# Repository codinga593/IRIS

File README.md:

# IRIS
IRIS Is a high powered model rocket focused on a precise propulsive landing on a custom tower, similar to SpaceX's falcon 9. It will fly on a H45 motor to approximately 700m, guiding itself to a waypoint in the air using aerodynamic fin control. It will then begin a controlled descent where fins attempt to maintain x and y pos. A landing motor (F15) then ignites to kill velocity, as thrust vectoring helps guide it to the tower where it will be caught by two motorised arms.

This project, while ambitous will be split into serveral mid power and high power flights to test subsystems and more. At the heart of the rocket is the amethyst flight computer, along with two extra boards- a compute module 5 and a raspberry pi zero 2 w. The compute module five will run non linear model predicitive control, an insanely powerful control algorithm to determine required X and Y accels to reach the target given fin or tvc limits. The STM32 based flight computer then turns these accelerations into concrete actuator commands. AN ADDED layer of abstraction is present for the fins in the form of field oriented control, which maintains torque to prevent backdriving.

Pictured above: FULL CAD of IRIS with transparent airframe for visibility

Pictured above: AMETHYST rocket flight computer. Note: Silkscreen colour is subject to change.

Pictured Above: Final Avionics Bay design on IRIS

# Bill of Materials (BOM)

| Designator | Part Name | Qty | Value / Part Number | Link |
|---|---:|---:|---|---|
| C66,C95,C26,C49,C28,C67,C55,C29,C33,C22,C48,C54,C19,C34,C30,C58,C41,C42,C20,C45,C46,C39,C18,C93,C47,C32,C21,C25,C27,C88,C35 | Ceramic Capacitor | 31 | 100nF, 0402, Samsung CL05B104KO5NNNC (JLC C1525) | [Link](https://jlcpcb.com/partdetail/1877-CL05B104KO5NNNC/C1525) |
| C23,C24,C61,C60 | Ceramic Capacitor | 4 | 24pF, 0402, C0G/NP0, FH 0402CG240J500NT (LCSC C1553) | [Link](https://www.lcsc.com/product-detail/C1553.html) |
| U3 | IMU | 1 | BNO085 (JLC C5189642) | [Link](https://jlcpcb.com/partdetail/CEVA-BNO085/C5189642) |
| J9,J1,J10,J11 | Socket Header | 4 | 1x03, 2.54mm, vertical, Amphenol SIP050-1X03-157BLF | [Link](https://www.digikey.com/en/products/detail/amphenol-cs-fci/SIP050-1X03-157BLF/1541044) |
| R45,R48,R46,R47,R49,R44 | Resistor | 6 | TBD - source BOM only says 'R' (exact value not specified) |  |
| R21,R14,R22,R17 | Resistor | 4 | 4.7kΩ, 0603, UNI-ROYAL 0603WAF4701T5E (LCSC C23162) | [Link](https://www.lcsc.com/product-detail/C23162.html) |
| TP13,TP9,TP14,TP6,TP11,TP10,TP16,TP15,TP5,TP8,TP7 | Test Point | 11 | PCB test pad 1.0x1.0mm - no discrete purchasable part specified |  |
| URpiZero1,UCM4 | Socket Header | 2 | 2x20 Raspberry Pi socket/riser header, Adafruit 4079 | [Link](https://www.digikey.com.au/en/products/detail/adafruit-industries-llc/4079/9858462) |
| R10,R18,R28 | Resistor | 3 | 100kΩ, 0402, UNI-ROYAL 0402WGF1003TCE (JLC/LCSC C25741) | [Link](https://www.lcsc.com/product-detail/C25741.html) |
| Q2,Q4,Q3 | MOSFET | 3 | BSZ100N06LS3 G, Infineon | [Link](https://www.digikey.com/en/products/detail/infineon-technologies/BSZ100N06LS3GATMA1/1936392) |
| C53,C92,C90,C94 | Ceramic Capacitor | 4 | 10uF, 0402, Samsung CL05A106MQ5NUNC (JLC C15525) | [Link](https://jlcpcb.com/partdetail/16204-CL05A106MQ5NUNC/C15525) |
| R6,R32,R8,R1 | Resistor | 4 | 100Ω, 0402, Ever Ohms CR0402F100RQ10 (JLC C429511) | [Link](https://jlcpcb.com/partdetail/Ever_OhmsTech-CR0402F100RQ10/C429511) |
| J14 | Pin Header | 1 | 1x04, 2.54mm, vertical, generic 4-pin header | [Link](https://newhavendisplay.com/1x4-single-row-pin-header-connector/) |
| J17 | RF Connector | 1 | Hirose U.FL-R-SMT(01) | [Link](https://www.digikey.com.au/en/products/detail/hirose-electric-co-ltd/U-FL-R-SMT-01/513010) |
| U5 | Barometer | 1 | MS5611-01BA03 / MS561101BA03-50 (JLC C15639) | [Link](https://jlcpcb.com/partdetail/TEConnectivity-MS561101BA0350/C15639) |
| C37 | Ceramic Capacitor | 1 | 10uF, 0603, Samsung CL10A106MA8NRNC (LCSC C96446) | [Link](https://www.lcsc.com/product-detail/C96446.html) |
| C91,C86,C89 | Ceramic Capacitor | 3 | 22uF, 0402, JLCPCB Assembly 22uF/16V (JLC C9900105298) | [Link](https://jlcpcb.com/partdetail/JLCPCBAssembly-22uF16V/C9900105298) |
| C84,C85 | Ceramic Capacitor | 2 | 10pF, 0402, FH 0402CG100J500NT (JLC C1545) | [Link](https://jlcpcb.com/partdetail/1897-0402CG100J500NT/C1545) |
| L11,L10,L9 | Inductor | 3 | 6.8uH, Würth WE-XHMA 6060 | [Link](https://www.mouser.com/ProductDetail/Wurth-Elektronik/74437368068) |
| R34,R33 | Resistor | 2 | 22Ω, 0402, YAGEO RC0402FR-0722RL (LCSC C114765) | [Link](https://www.lcsc.com/product-detail/C114765.html) |
| J5,J3,J4 | Terminal Block | 3 | Same Sky / CUI TB002-500-02BE | [Link](https://www.digikey.com.au/en/products/detail/same-sky-formerly-cui-devices/TB002-500-02BE/10064069) |
| Y1,Y3 | Crystal | 2 | 24MHz, 3225, Suzhou Liming 3225-24.00-20-10-10/A (JLC C518165) | [Link](https://jlcpcb.com/partdetail/534702-3225_24_00_20_10_10A/C518165) |
| C31 | Ceramic Capacitor | 1 | 10uF, 0402, Samsung CL05A106MQ5NUNC (JLC C15525) | [Link](https://jlcpcb.com/partdetail/16204-CL05A106MQ5NUNC/C15525) |
| J6 | JST Header | 1 | JST B5B-XH-A, 5-pin, 2.50mm, vertical | [Link](https://www.digikey.com/en/products/detail/jst-sales-america-inc/B5B-XH-A/1530483) |
| IC2 | LoRa Module | 1 | Seeed 114993390 / Wio-SX1262 | [Link](https://www.digikey.com/en/products/detail/seeed-technology-co-ltd/114993390/25835823) |
| U2 | LDO Regulator | 1 | AMS1117-3.3, SOT-223 (JLC C6186) | [Link](https://jlcpcb.com/partdetail/Advanced_MonolithicSystems-AMS1117_33/C6186) |
| U4 | IMU | 1 | ICM-42688-P (JLC C1850418) | [Link](https://jlcpcb.com/partdetail/TDKInvenSense-ICM_42688P/C1850418) |
| U11,U12,U13 | Buck Converter | 3 | TPS54525PWPR (JLC C140350) | [Link](https://jlcpcb.com/partdetail/TexasInstruments-TPS54525PWPR/C140350) |
| C36,C38,C56 | Ceramic Capacitor | 3 | 100nF, 0603, YAGEO CC0603KRX7R9BB104 (LCSC C14663) | [Link](https://www.lcsc.com/product-detail/C14663.html) |
| IC1 | NOR Flash | 1 | W25Q128JVFIQ (JLC C111478) | [Link](https://jlcpcb.com/partdetail/WinbondElec-W25Q128JVFIQ/C111478) |
| R15,R2,R7,R9,R11,R5,R29,R12,R27 | Resistor | 9 | 10kΩ, 0402, UNI-ROYAL 0402WGF1002TCE (JLC C25744) | [Link](https://jlcpcb.com/partdetail/26487-0402WGF1002TCE/C25744) |
| R3,R4 | Resistor | 2 | 1.5kΩ, 0402, UNI-ROYAL 0402WGF1501TCE (LCSC C25867) | [Link](https://www.lcsc.com/product-detail/C25867.html) |
| U1 | MCU | 1 | STM32H753ZIT6 (JLC C730207) | [Link](https://jlcpcb.com/partdetail/STMicroelectronics-STM32H753ZIT6/C730207) |
| C3,C2 | Ceramic Capacitor | 2 | 22uF, 0805, Samsung CL21A226MAYNNNE (LCSC C45783) | [Link](https://www.lcsc.com/product-detail/C45783.html) |
| C59 | Ceramic Capacitor | 1 | 10nF, 0402, Kyocera AVX 0402YC103K4T2A (JLC C2172121) | [Link](https://jlcpcb.com/partdetail/KyoceraAVX-0402YC103K4T2A/C2172121) |
| Y4 | Crystal | 1 | TBD - source BOM says only 'Crystal' in 2012 package |  |
| IC7 | Radar Sensor | 1 | Acconeer A121-001-T&R / A121 | [Link](https://www.mouser.com/ProductDetail/Acconeer/A121-001-TR) |
| D2 | LED | 1 | TBD - source BOM says only 'LED' in 0402 package |  |
| C1 | Ceramic Capacitor | 1 | 10uF, 0402, Samsung CL05A106MQ5NUNC (JLC C15525) | [Link](https://jlcpcb.com/partdetail/16204-CL05A106MQ5NUNC/C15525) |
| J7 | Molex PicoBlade Header | 1 | Molex 53261-0471 | [Link](https://www.digikey.com/en/products/detail/molex/0532610471/699096) |
| C40,C17 | Ceramic Capacitor | 2 | 2.2uF, 0402, Samsung CL05A225MQ5NSNC (JLC C12530) | [Link](https://jlcpcb.com/partdetail/13164-CL05A225MQ5NSNC/C12530) |
| J18 | USB Connector | 1 | Würth 629105150521, Micro USB B | [Link](https://www.digikey.com.au/en/products/detail/w%C3%BCrth-elektronik/629105150521/5047751) |
| U7 | Level Shifter | 1 | TXS0108EPWR (JLC C17206) | [Link](https://jlcpcb.com/partdetail/TexasInstruments-TXS0108EPWR/C17206) |
| FB1 | Ferrite Bead | 1 | Sunlord GZ1608D601TF (JLC C1002) | [Link](https://jlcpcb.com/partdetail/Sunlord-GZ1608D601TF/C1002) |
| D3 | Schottky Diode | 1 | BAT54A, SOT-23 (JLC C397609) | [Link](https://jlcpcb.com/partdetail/AnBon-BAT54A/C397609) |
| J12 | JST Header | 1 | JST S2B-XH-A, 2-pin, 2.50mm, right-angle | [Link](https://www.digikey.com/en/products/detail/jst-sales-america-inc/S2B-XH-A/1651055) |
| U10 | GNSS Module | 1 | u-blox MAX-M10S-00B (JLC C4153167) | [Link](https://jlcpcb.com/partdetail/UBLOX-MAX_M10S00B/C4153167) |
| J8 | XT30 Connector | 1 | AMASS XT30U-M (JLC C99101) | [Link](https://jlcpcb.com/partdetail/Changzhou_AmassElec-XT30UM/C99101) |
| R20,R19 | Resistor | 2 | 10kΩ, 0603, YAGEO RC0603FR-0710KL (LCSC C98220) | [Link](https://www.lcsc.com/product-detail/C98220.html) |
| J2 | JST Header | 1 | JST B2B-XH-A, 2-pin, 2.50mm, vertical | [Link](https://www.digikey.com/en/products/detail/jst-sales-america-inc/B2B-XH-A/1651045) |

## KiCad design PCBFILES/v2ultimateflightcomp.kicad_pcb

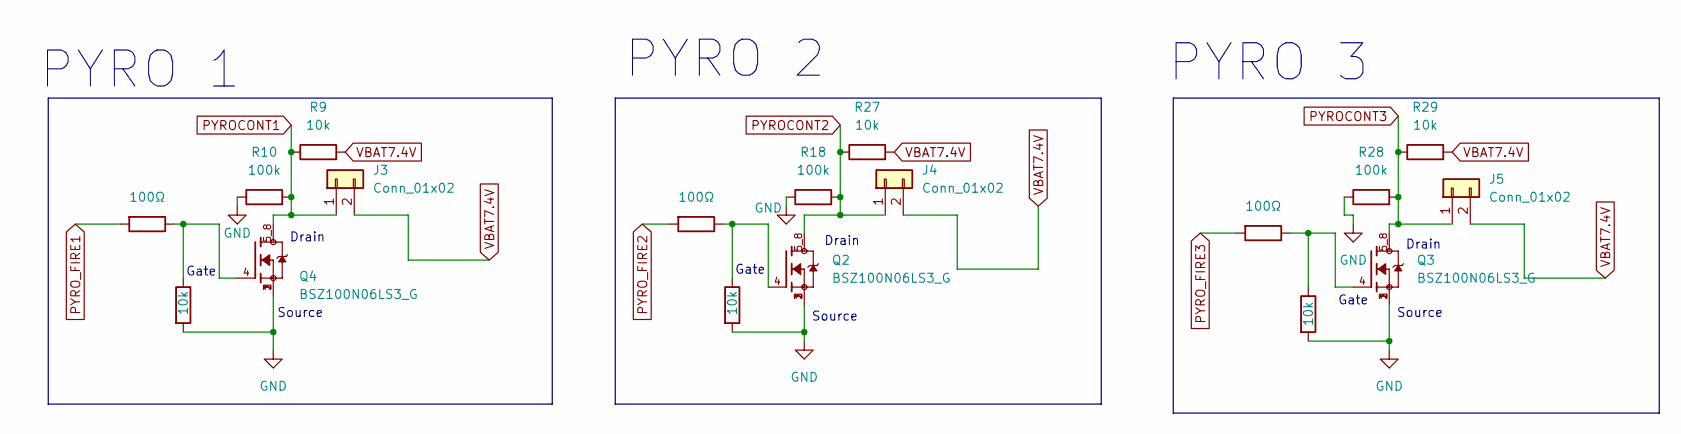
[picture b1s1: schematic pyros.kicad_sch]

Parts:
J3, J4, J5: Conn_01x02; CUI_TB002-500-02BE
Q2, Q3, Q4: BSZ100N06LS3_G; TRANS_BSZ100N06LS3_G; PARTREV 2.4
R1, R6, R8: 100Ω; R_0402_1005Metric
R2, R5, R7, R9, R27, R29: 10k; R_0402_1005Metric
R10, R18, R28: 100k; R_0402_1005Metric

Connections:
GND: Q2.1, Q2.2, Q2.3, Q3.1, Q3.2, Q3.3, Q4.1, Q4.2, Q4.3, R2.2, R5.2, R7.2, R10.1, R18.1, R28.1; also elsewhere on the board
unnamed: Q2.4, R5.1, R6.1
unnamed: Q3.4, R7.1, R8.1
unnamed: Q4.4, R1.1, R2.1
PYROCONT1: J3.1, Q4.5_8, R9.1, R10.2; also elsewhere on the board
PYROCONT2: J4.1, Q2.5_8, R18.2, R27.1; also elsewhere on the board
PYROCONT3: J5.1, Q3.5_8, R28.2, R29.1; also elsewhere on the board
PYRO_FIRE1: R1.2; also elsewhere on the board
PYRO_FIRE2: R6.2; also elsewhere on the board
PYRO_FIRE3: R8.2; also elsewhere on the board
VBAT7.4V: J3.2, J4.2, J5.2, R9.2, R27.2, R29.2; also elsewhere on the board

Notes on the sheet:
PYRO 3
Gate
PYRO 2
Source
Drain
PYRO 1

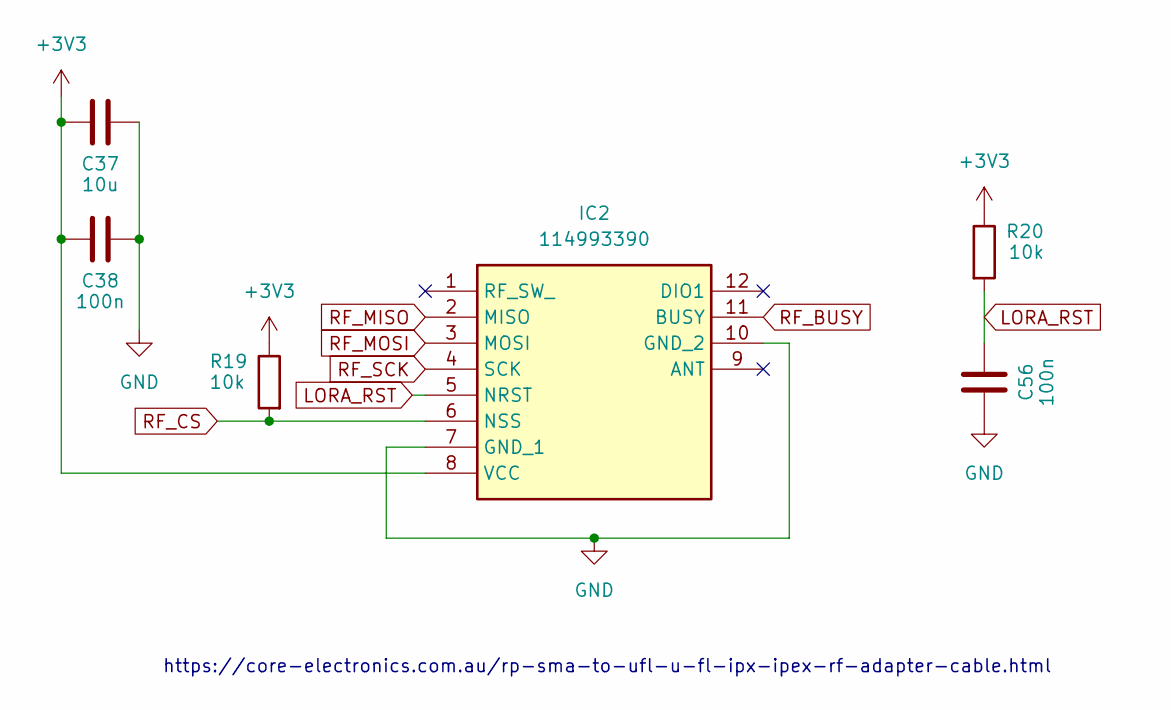
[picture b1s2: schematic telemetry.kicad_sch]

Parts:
C37: 10u; C_0603_1608Metric
C38, C56: 100n; C_0603_1608Metric
IC2: 114993390; Mouser Part Number 713-114993390
R19, R20: 10k; R_0603_1608Metric

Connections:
+3V3: C37.1, C38.1, IC2.8 (VCC), R19.1, R20.1; also elsewhere on the board
GND: C37.2, C38.2, C56.1, IC2.7 (GND_1), IC2.10 (GND_2); also elsewhere on the board
LORA_RST: C56.2, IC2.5 (NRST), R20.2; also elsewhere on the board
RF_BUSY: IC2.11 (BUSY); also elsewhere on the board
RF_CS: IC2.6 (NSS), R19.2; also elsewhere on the board
RF_MISO: IC2.2 (MISO); also elsewhere on the board
RF_MOSI: IC2.3 (MOSI); also elsewhere on the board
RF_SCK: IC2.4 (SCK); also elsewhere on the board

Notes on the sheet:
https://core-electronics.com.au/rp-sma-to-ufl-u-fl-ipx-ipex-rf-adapter-cable.html

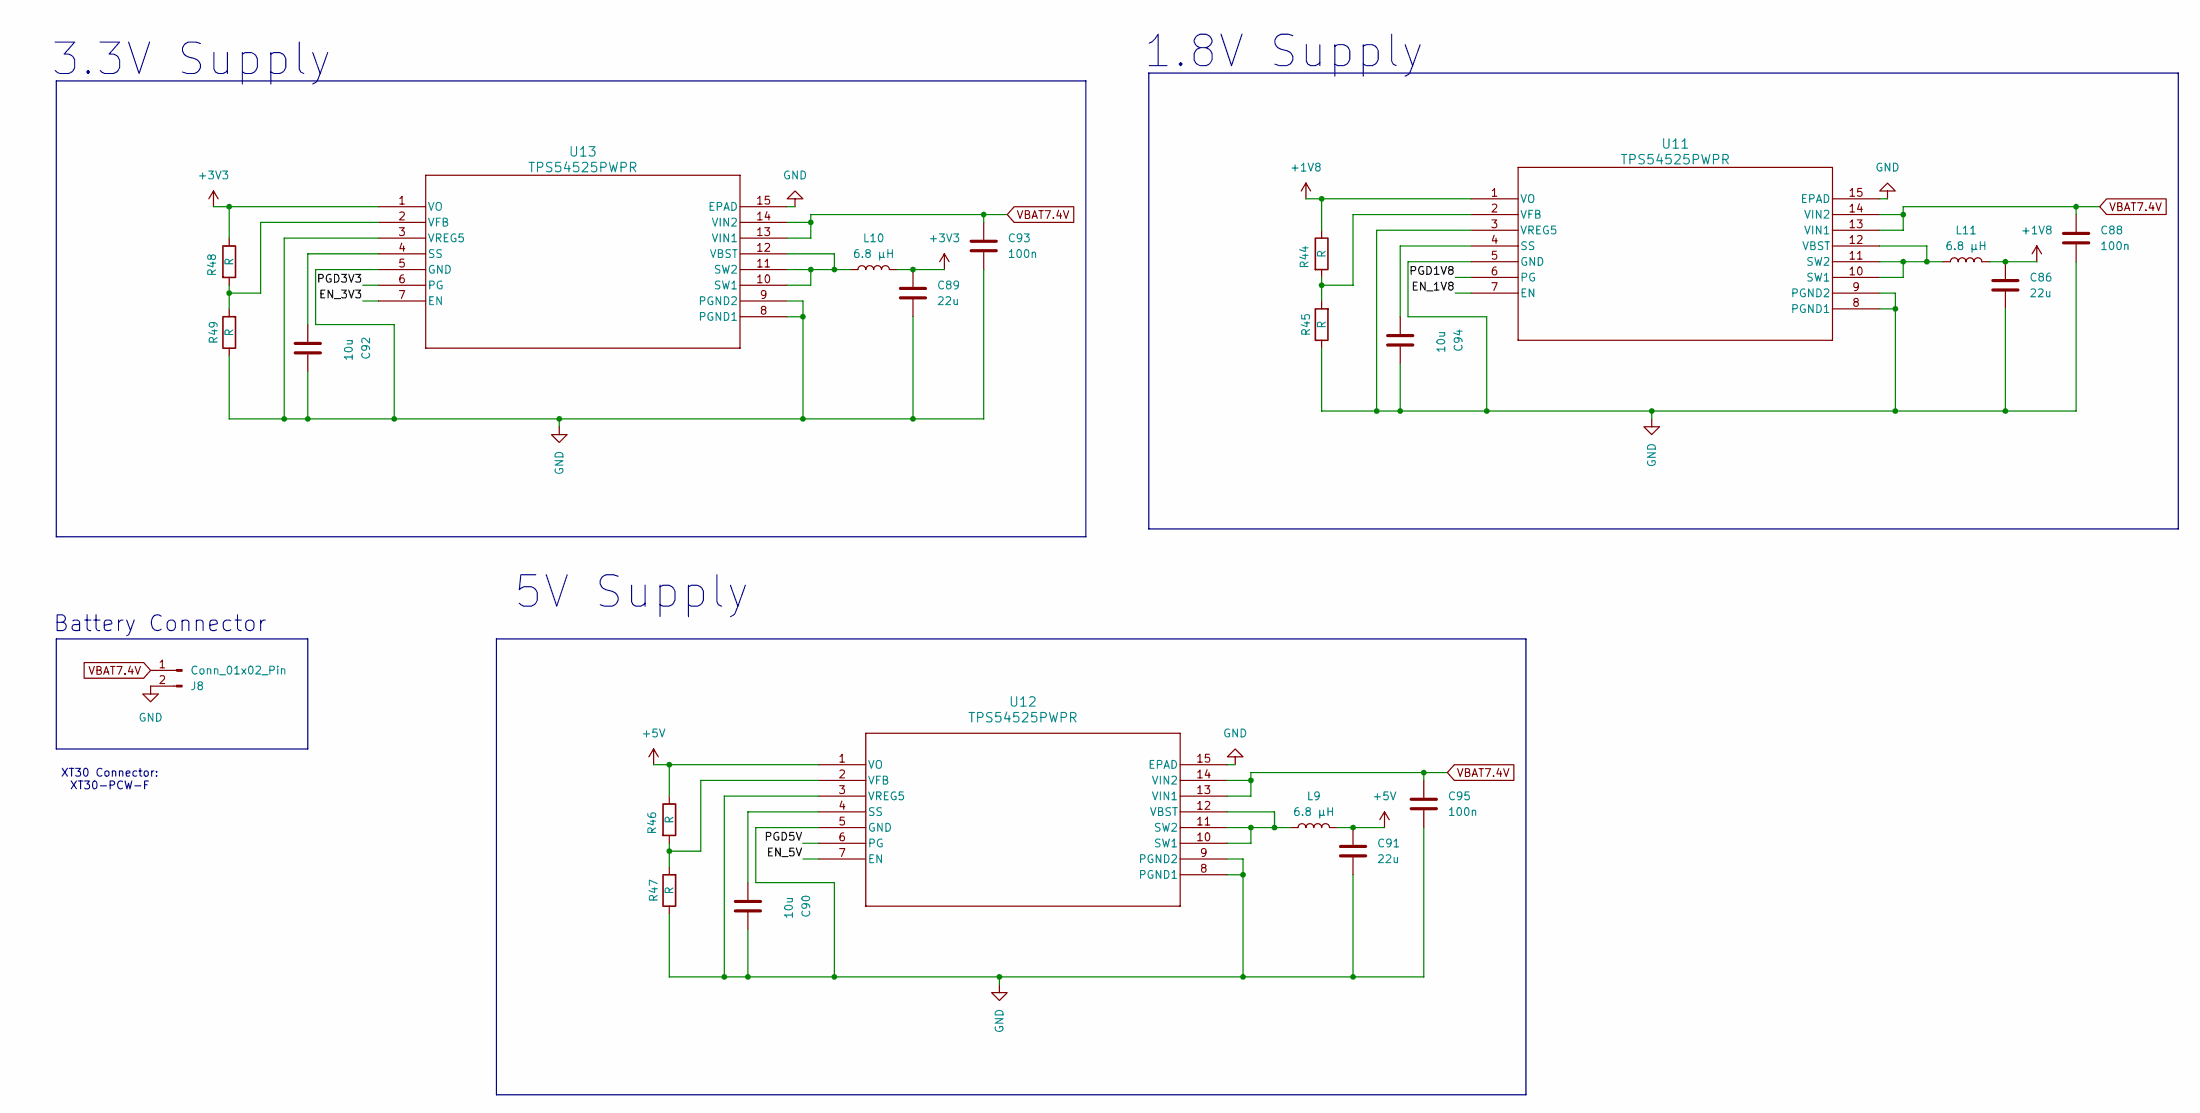
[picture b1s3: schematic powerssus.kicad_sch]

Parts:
C86, C89, C91: 22u; C_0402_1005Metric
C88, C93, C95: 100n; C_0402_1005Metric
C90, C92, C94: 10u; C_0402_1005Metric
J8: Conn_01x02_Pin; AMASS_XT30U-M_1x02_P5.0mm_Vertical
L9, L10, L11: 6.8 µH; WE-XHMA_6060
R44, R45, R46, R47, R48, R49: R; R_0402_1005Metric
U11, U12, U13: TPS54525PWPR; PWP14_2P31X2P46_TEX

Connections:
+1V8: C86.1, L11.2, R44.1, U11.1 (VO); also elsewhere on the board
+3V3: C89.1, L10.2, R48.1, U13.1 (VO); also elsewhere on the board
+5V: C91.1, L9.2, R46.1, U12.1 (VO); also elsewhere on the board
/Power/EN_1V8: U11.7 (EN)
/Power/EN_3V3: U13.7 (EN)
/Power/EN_5V: U12.7 (EN)
/Power/PGD1V8: U11.6 (PG)
/Power/PGD3V3: U13.6 (PG)
/Power/PGD5V: U12.6 (PG)
GND: C86.2, C88.2, C89.2, C90.1, C91.2, C92.1, C93.2, C94.1, C95.2, J8.2, R45.1, R47.1, R49.1, U11.3 (VREG5), U11.5 (GND), U11.8 (PGND1), U11.9 (PGND2), U11.15 (EPAD), U12.3 (VREG5), U12.5 (GND), U12.8 (PGND1), U12.9 (PGND2), U12.15 (EPAD), U13.3 (VREG5), U13.5 (GND), U13.8 (PGND1), U13.9 (PGND2), U13.15 (EPAD); also elsewhere on the board
unnamed: C94.2, U11.4 (SS)
unnamed: L11.1, U11.10 (SW1), U11.11 (SW2), U11.12 (VBST)
unnamed: R44.2, R45.2, U11.2 (VFB)
unnamed: C90.2, U12.4 (SS)
unnamed: L9.1, U12.10 (SW1), U12.11 (SW2), U12.12 (VBST)
unnamed: R46.2, R47.2, U12.2 (VFB)
unnamed: C92.2, U13.4 (SS)
unnamed: L10.1, U13.10 (SW1), U13.11 (SW2), U13.12 (VBST)
unnamed: R48.2, R49.2, U13.2 (VFB)
VBAT7.4V: C88.1, C93.1, C95.1, J8.1, U11.13 (VIN1), U11.14 (VIN2), U12.13 (VIN1), U12.14 (VIN2), U13.13 (VIN1), U13.14 (VIN2); also elsewhere on the board

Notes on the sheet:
5V Supply
1.8V Supply
XT30 Connector: XT30-PCW-F
3.3V Supply
Battery Connector

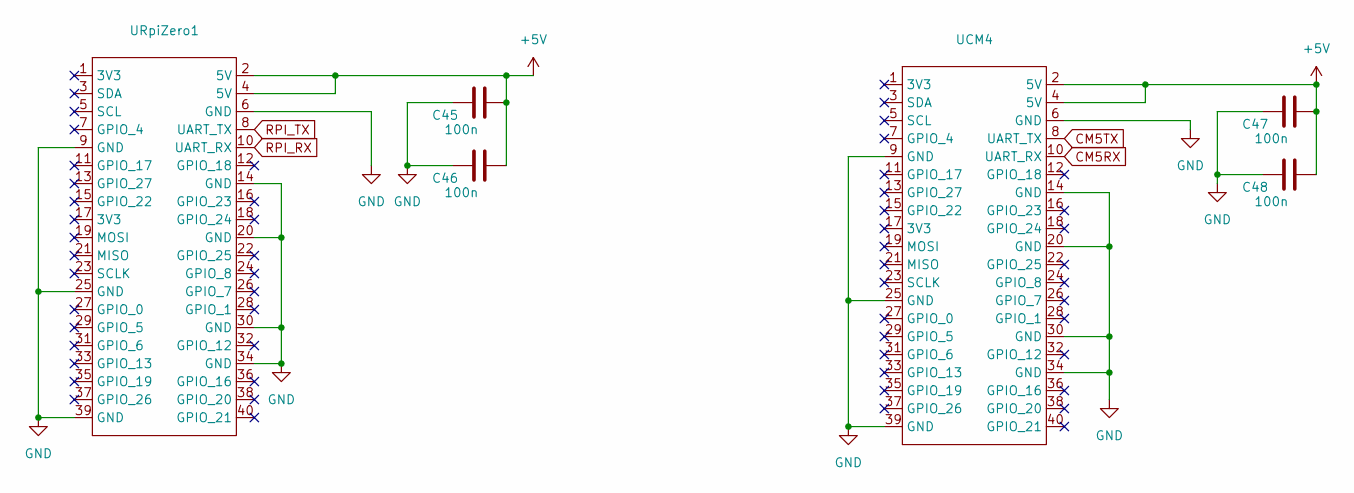
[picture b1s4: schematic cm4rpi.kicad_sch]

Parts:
C45, C46, C47, C48: 100n; C_0402_1005Metric
UCM4: PinSocket_2x20_P2.54mm_Vertical_SMD
URpiZero1: PinSocket_2x20_P2.54mm_Vertical_SMD

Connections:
+5V: C45.2, C46.2, C47.2, C48.2, UCM4.2 (5V), UCM4.4 (5V), URpiZero1.2 (5V), URpiZero1.4 (5V); also elsewhere on the board
CM5RX: UCM4.10 (UART_RX); also elsewhere on the board
CM5TX: UCM4.8 (UART_TX); also elsewhere on the board
GND: C45.1, C46.1, C47.1, C48.1, UCM4.6 (GND), UCM4.9 (GND), UCM4.14 (GND), UCM4.20 (GND), UCM4.25 (GND), UCM4.30 (GND), UCM4.34 (GND), UCM4.39 (GND), URpiZero1.6 (GND), URpiZero1.9 (GND), URpiZero1.14 (GND), URpiZero1.20 (GND), URpiZero1.25 (GND), URpiZero1.30 (GND), URpiZero1.34 (GND), URpiZero1.39 (GND); also elsewhere on the board
RPI_RX: URpiZero1.10 (UART_RX); also elsewhere on the board
RPI_TX: URpiZero1.8 (UART_TX); also elsewhere on the board

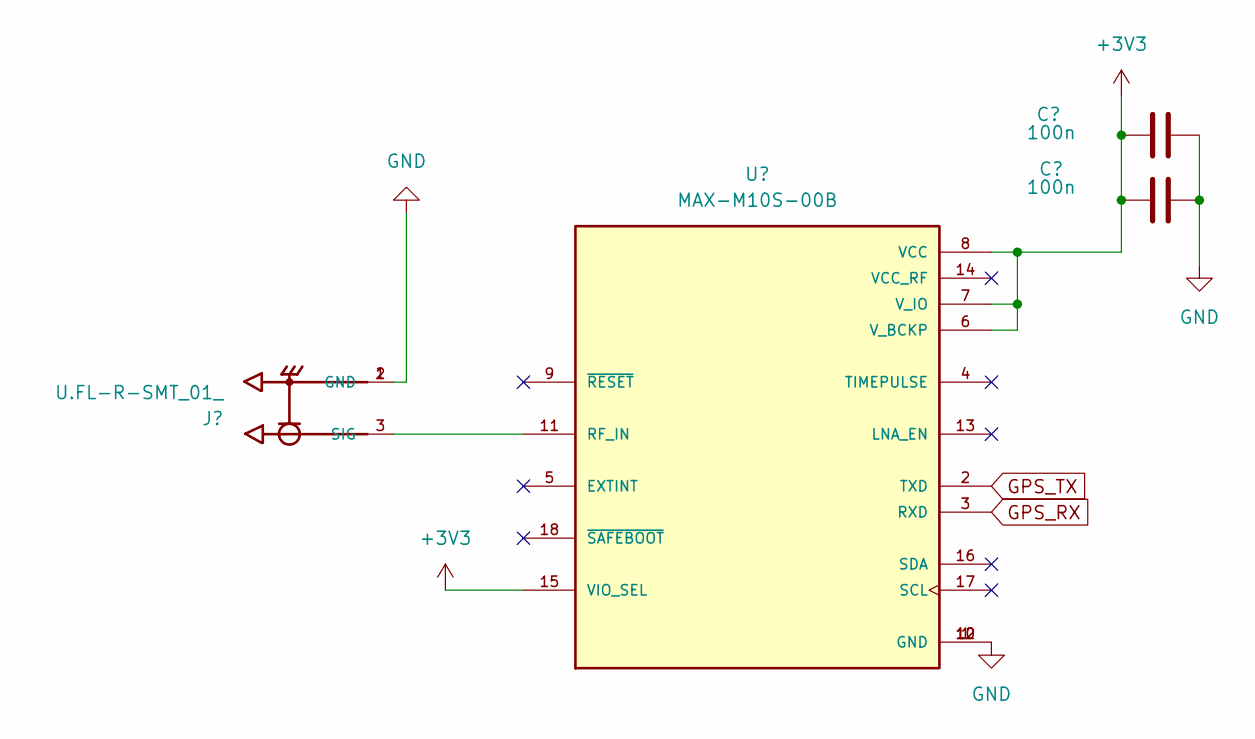
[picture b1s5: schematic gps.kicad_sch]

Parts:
C54, C55: 100n; C_0402_1005Metric
J17: U.FL-R-SMT_01_; HRS_U.FL-R-SMT_01_
U10: MAX-M10S-00B; XCVR_MAX-M10S-00B; PARTREV C1

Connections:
+3V3: C54.1, C55.1, U10.6 (V_BCKP), U10.7 (V_IO), U10.8 (VCC), U10.15 (VIO_SEL); also elsewhere on the board
GND: C54.2, C55.2, J17.1 (GND), J17.2 (GND), U10.1 (GND), U10.10 (GND), U10.12 (GND); also elsewhere on the board
GPS_RX: U10.3 (RXD); also elsewhere on the board
GPS_TX: U10.2 (TXD); also elsewhere on the board
unnamed: J17.3 (SIG), U10.11 (RF_IN)

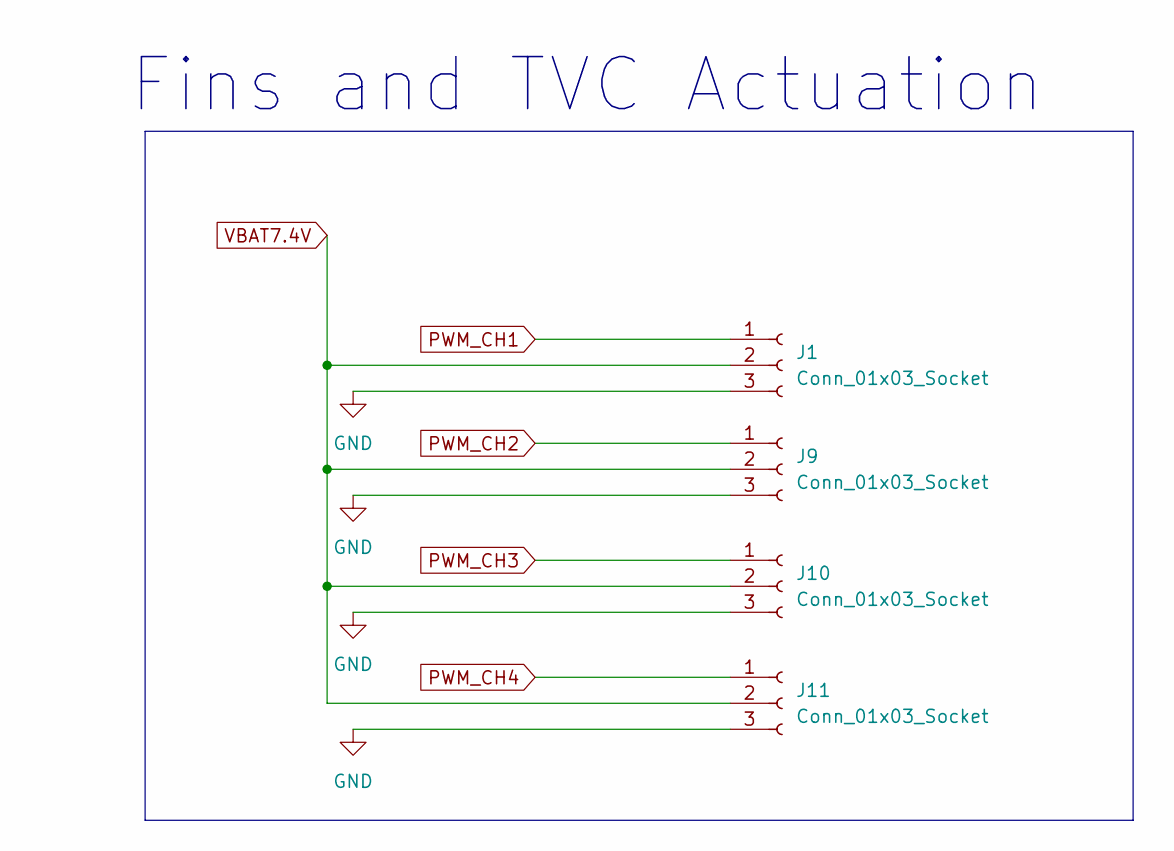
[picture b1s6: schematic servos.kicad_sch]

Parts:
J1, J9, J10, J11: Conn_01x03_Socket; PinHeader_1x03_P2.54mm_Vertical

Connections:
GND: J1.3, J9.3, J10.3, J11.3; also elsewhere on the board
PWM_CH1: J1.1; also elsewhere on the board
PWM_CH2: J9.1; also elsewhere on the board
PWM_CH3: J10.1; also elsewhere on the board
PWM_CH4: J11.1; also elsewhere on the board
VBAT7.4V: J1.2, J9.2, J10.2, J11.2; also elsewhere on the board

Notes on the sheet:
Fins and TVC Actuation

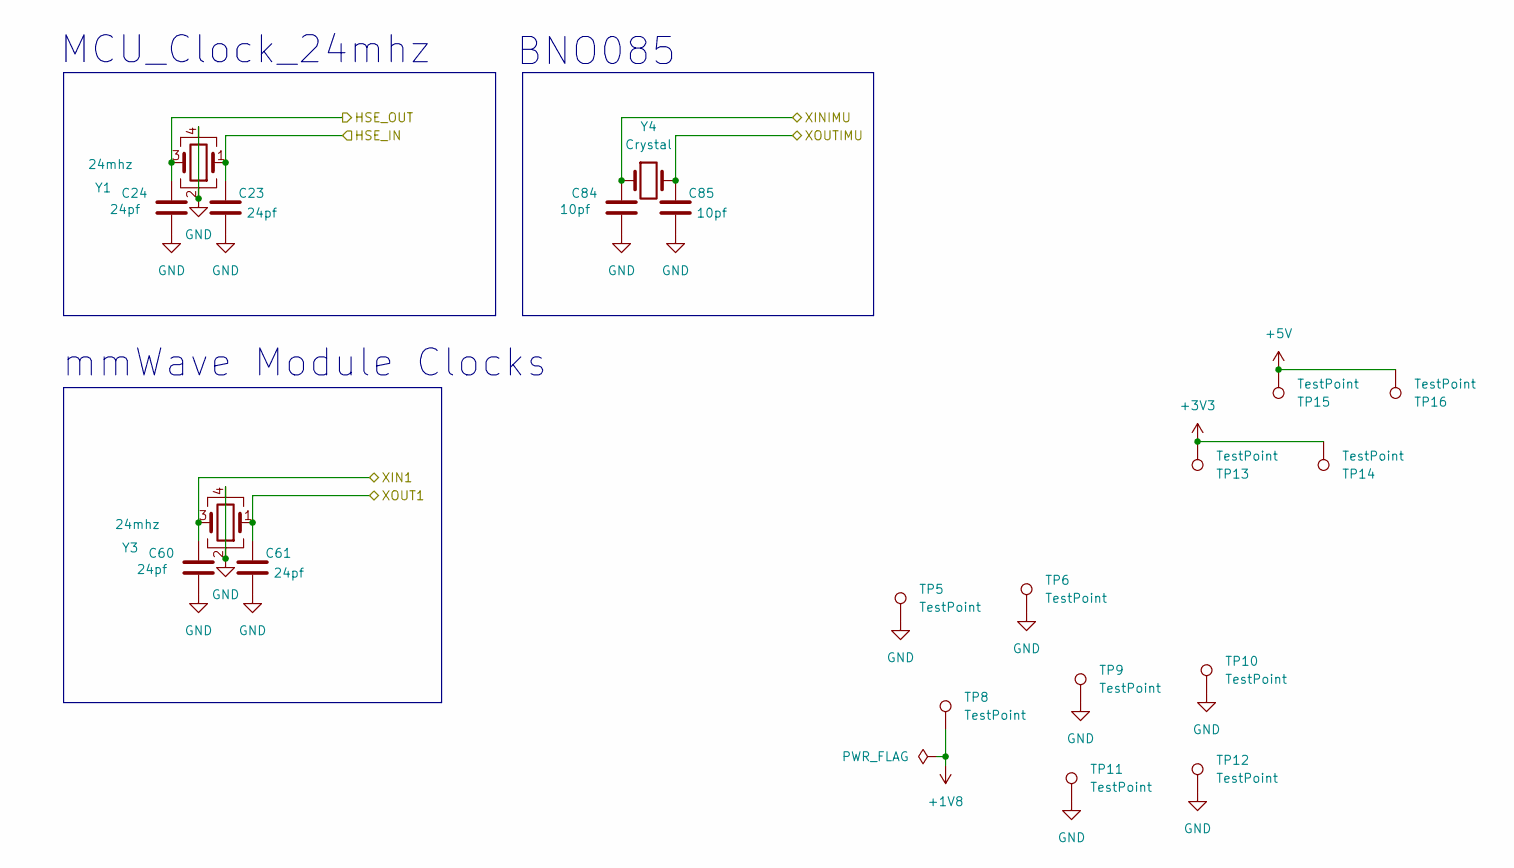
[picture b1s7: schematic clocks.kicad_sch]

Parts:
C23, C24, C60, C61: 24pf; C_0402_1005Metric
C84, C85: 10pf; C_0402_1005Metric
TP5, TP6, TP8, TP9, TP10, TP11, TP12, TP13, TP14, TP15, TP16: TestPoint; TestPoint_Pad_1.0x1.0mm
Y1, Y3: 24mhz; TSX-3225
Y4: Crystal; Crystal_SMD_2012-2Pin_2.0x1.2mm

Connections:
+1V8: TP8.1; also elsewhere on the board
+3V3: TP13.1, TP14.1; also elsewhere on the board
+5V: TP15.1, TP16.1; also elsewhere on the board
/Clocks/HSE_IN: C23.1, Y1.1; also elsewhere on the board
/Clocks/HSE_OUT: C24.1, Y1.3; also elsewhere on the board
/Clocks/XIN1: C60.1, Y3.3; also elsewhere on the board
/Clocks/XINIMU: C84.1, Y4.1; also elsewhere on the board
/Clocks/XOUT1: C61.1, Y3.1; also elsewhere on the board
/Clocks/XOUTIMU: C85.1, Y4.2; also elsewhere on the board
GND: C23.2, C24.2, C60.2, C61.2, C84.2, C85.2, TP5.1, TP6.1, TP9.1, TP10.1, TP11.1, TP12.1, Y1.2, Y1.4, Y3.2, Y3.4; also elsewhere on the board

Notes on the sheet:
mmWave Module Clocks
BNO085
MCU_Clock_24mhz

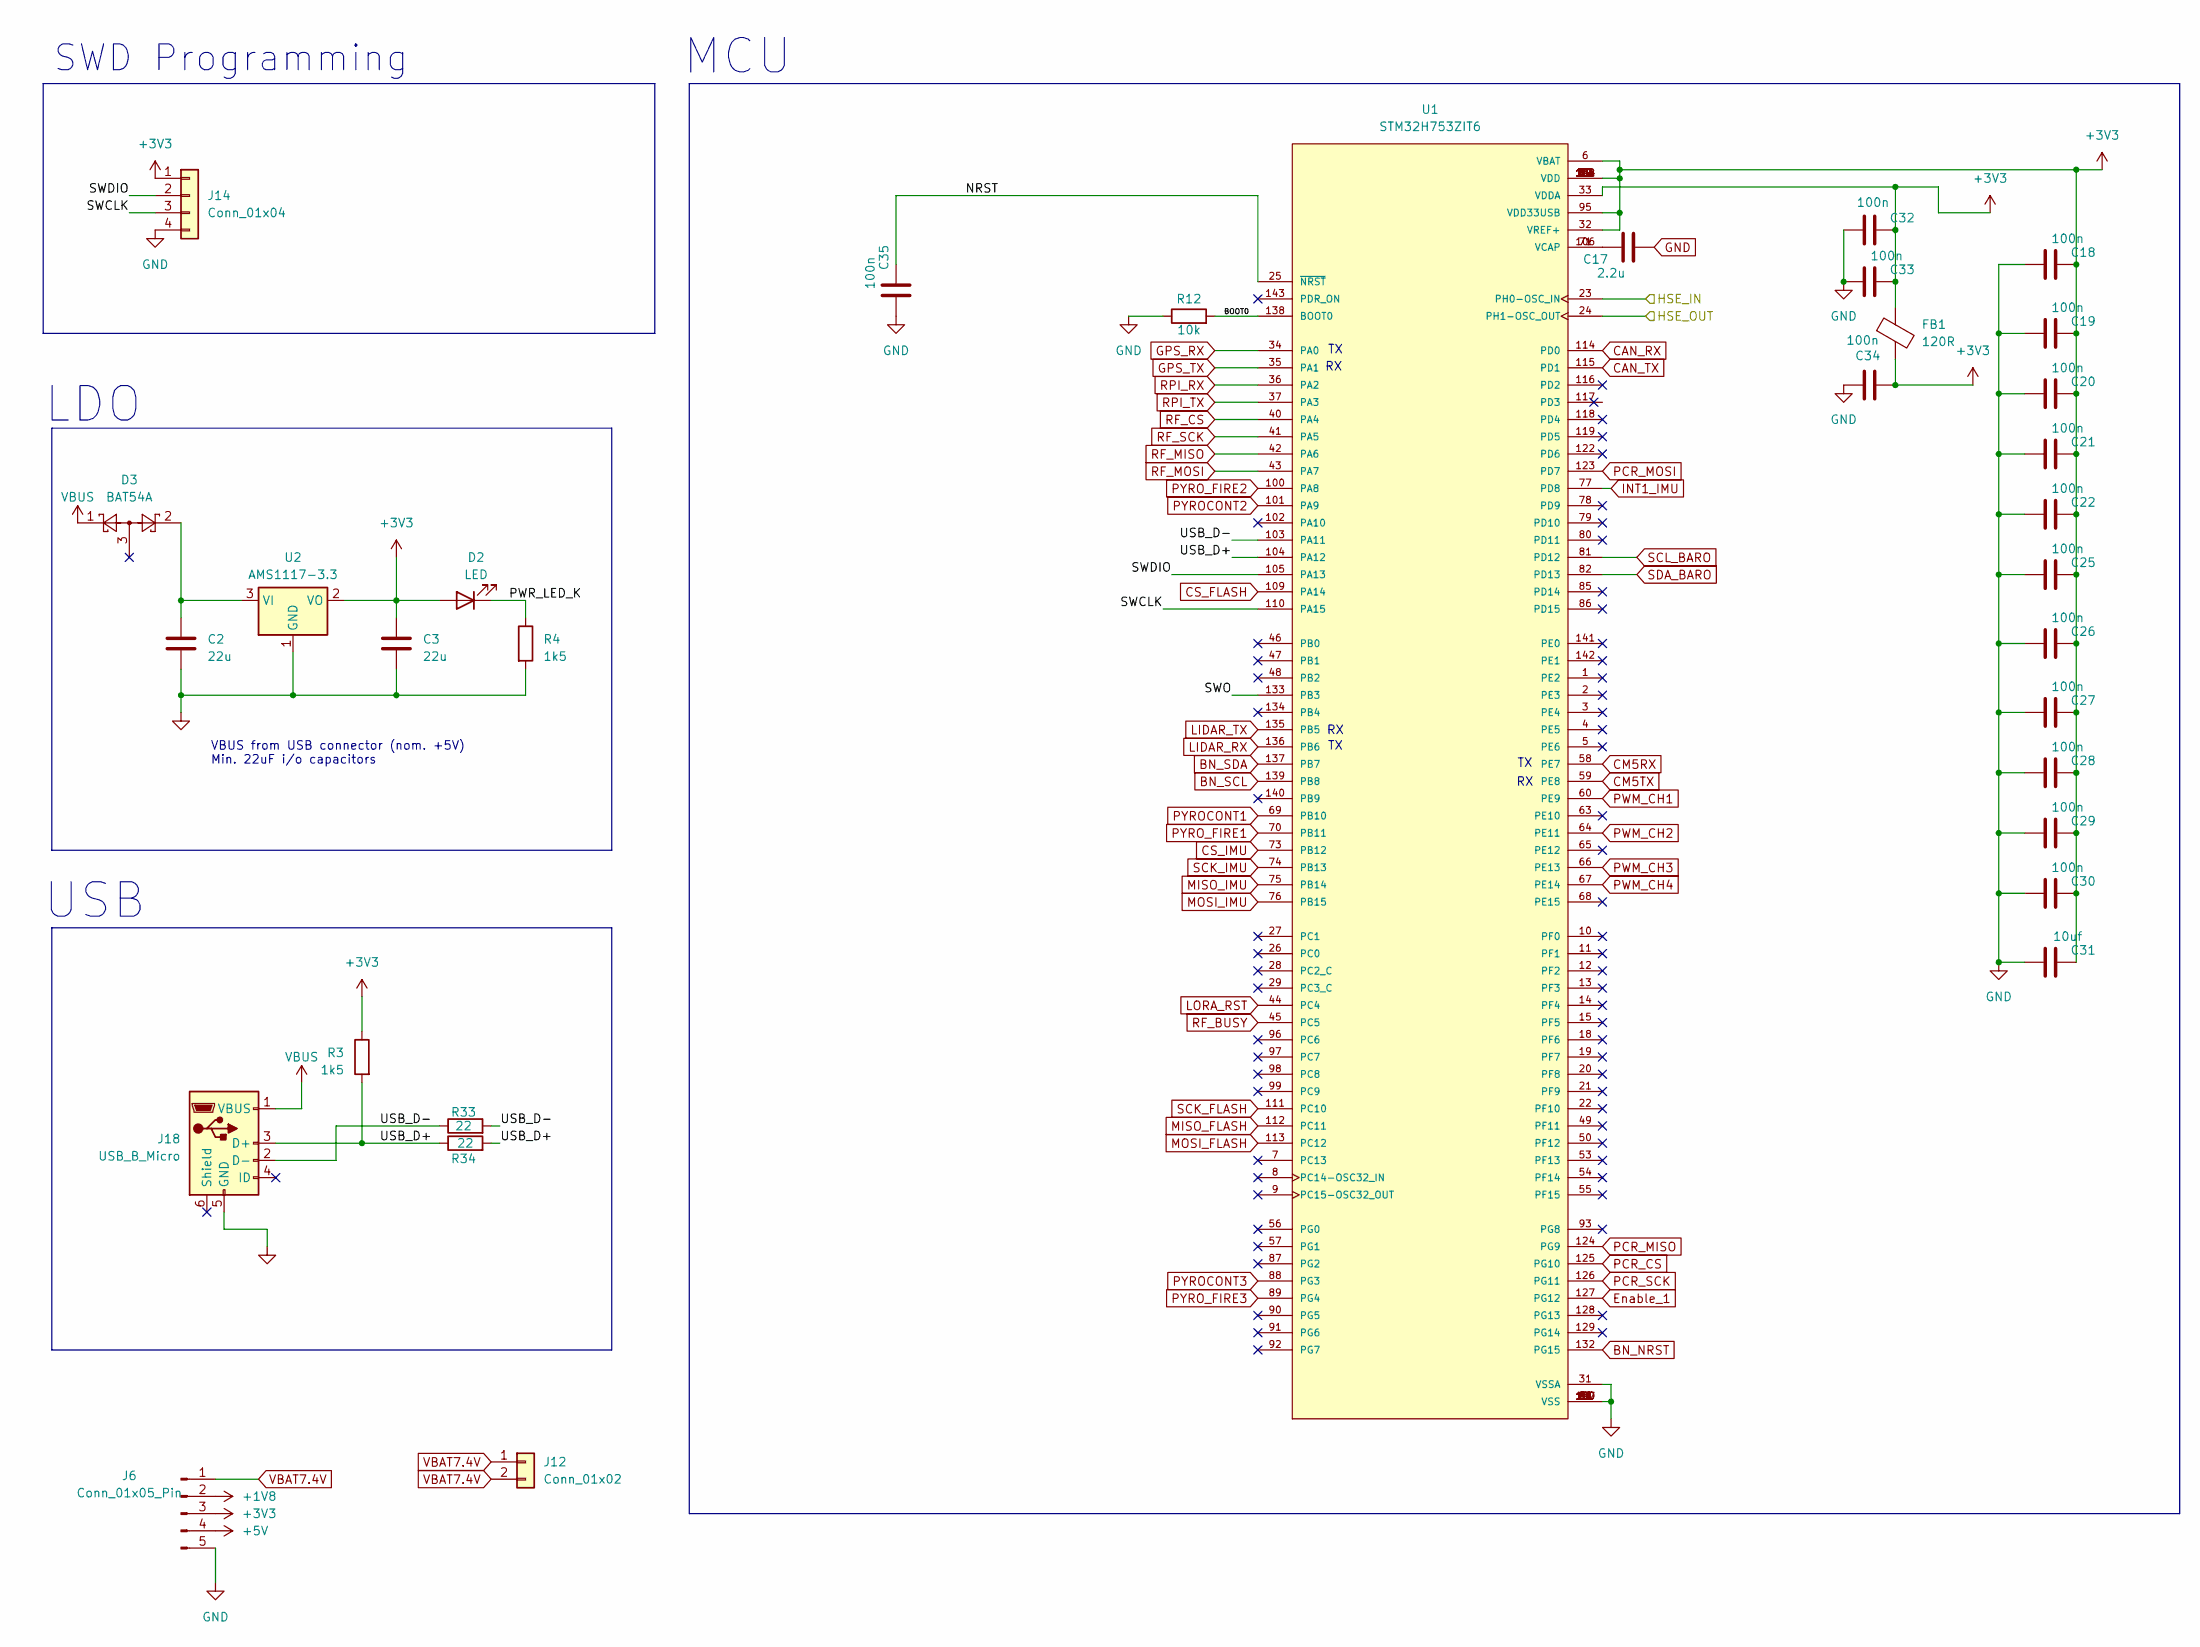
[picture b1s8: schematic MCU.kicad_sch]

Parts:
C2, C3: 22u; C_0805_2012Metric
C17: 2.2u; C_0402_1005Metric
C18, C19, C20, C21, C22, C25, C26, C27, C28, C29, C30, C32, C33, C34, C35: 100n; C_0402_1005Metric
C31: 10uf; C_0402_1005Metric
D2: LED; LED_0402_1005Metric
D3: BAT54A; SOT-23
FB1: 120R; IND_GZ1608_SNL
J6: Conn_01x05_Pin; JST_XH_B5B-XH-A_1x05_P2.50mm_Vertical
J12: Conn_01x02; JST_XH_S2B-XH-A_1x02_P2.50mm_Horizontal
J14: Conn_01x04; PinHeader_1x04_P2.54mm_Vertical
J18: USB_B_Micro; USB_Micro-B_Wuerth_629105150521
R3, R4: 1k5; R_0402_1005Metric
R12: 10k; R_0402_1005Metric
R33, R34: 22; R_0402_1005Metric
U1: STM32H753ZIT6; QFP50P2200X2200X160-144N; PARTREV 7
U2: AMS1117-3.3; SOT-223-3_TabPin2

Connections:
+1V8: J6.2; also elsewhere on the board
+3V3: C3.1, C18.1, C19.1, C20.1, C21.1, C22.1, C25.1, C26.1, C27.1, C28.1, C29.1, C30.1, C31.1, C32.1, C33.1, C34.1, D2.2 (A), FB1.1, FB1.2, J6.3, J14.1, R3.1, U1.6 (VBAT), U1.17 (VDD), U1.30 (VDD), U1.32 (VREF+), U1.33 (VDDA), U1.39 (VDD), U1.52 (VDD), U1.62 (VDD), U1.72 (VDD), U1.84 (VDD), U1.95 (VDD33USB), U1.108 (VDD), U1.121 (VDD), U1.131 (VDD), U1.144 (VDD), U2.2 (VO); also elsewhere on the board
+5V: J6.4; also elsewhere on the board
/Clocks/HSE_IN: U1.23 (PH0-OSC_IN); also elsewhere on the board
/Clocks/HSE_OUT: U1.24 (PH1-OSC_OUT); also elsewhere on the board
/MCU/BOOT0: R12.2, U1.138 (BOOT0)
/MCU/NRST: C35.1, U1.25 (~NRST)
/MCU/PWR_LED_K: D2.1 (K), R4.1
/MCU/SWCLK: J14.3, U1.110 (PA15)
/MCU/SWDIO: J14.2, U1.105 (PA13)
/MCU/SWO: U1.133 (PB3)
/MCU/USB_D+: J18.3 (D+), R3.2, R34.1, R34.2, U1.104 (PA12)
/MCU/USB_D-: J18.2 (D-), R33.1, R33.2, U1.103 (PA11)
BN_NRST: U1.132 (PG15); also elsewhere on the board
BN_SCL: U1.139 (PB8); also elsewhere on the board
BN_SDA: U1.137 (PB7); also elsewhere on the board
CAN_RX: U1.114 (PD0); also elsewhere on the board
CAN_TX: U1.115 (PD1); also elsewhere on the board
CM5RX: U1.58 (PE7); also elsewhere on the board
CM5TX: U1.59 (PE8); also elsewhere on the board
CS_FLASH: U1.109 (PA14); also elsewhere on the board
CS_IMU: U1.73 (PB12); also elsewhere on the board
Enable_1: U1.127 (PG12); also elsewhere on the board
GND: C2.2, C3.2, C17.2, C18.2, C19.2, C20.2, C21.2, C22.2, C25.2, C26.2, C27.2, C28.2, C29.2, C30.2, C31.2, C32.2, C33.2, C34.2, C35.2, J6.5, J14.4, J18.5 (GND), R4.2, R12.1, U1.16 (VSS), U1.31 (VSSA), U1.38 (VSS), U1.51 (VSS), U1.61 (VSS), U1.83 (VSS), U1.94 (VSS), U1.107 (VSS), U1.120 (VSS), U1.130 (VSS), U2.1 (GND); also elsewhere on the board
GPS_RX: U1.34 (PA0); also elsewhere on the board
GPS_TX: U1.35 (PA1); also elsewhere on the board
INT1_IMU: U1.77 (PD8); also elsewhere on the board
LIDAR_RX: U1.136 (PB6); also elsewhere on the board
LIDAR_TX: U1.135 (PB5); also elsewhere on the board
LORA_RST: U1.44 (PC4); also elsewhere on the board
MISO_FLASH: U1.112 (PC11); also elsewhere on the board
MISO_IMU: U1.75 (PB14); also elsewhere on the board
MOSI_FLASH: U1.113 (PC12); also elsewhere on the board
MOSI_IMU: U1.76 (PB15); also elsewhere on the board
unnamed: C17.1, U1.71 (VCAP), U1.106 (VCAP)
unnamed: C2.1, D3.2, U2.3 (VI)
PCR_CS: U1.125 (PG10); also elsewhere on the board
PCR_MISO: U1.124 (PG9); also elsewhere on the board
PCR_MOSI: U1.123 (PD7); also elsewhere on the board
PCR_SCK: U1.126 (PG11); also elsewhere on the board
PWM_CH1: U1.60 (PE9); also elsewhere on the board
PWM_CH2: U1.64 (PE11); also elsewhere on the board
PWM_CH3: U1.66 (PE13); also elsewhere on the board
PWM_CH4: U1.67 (PE14); also elsewhere on the board
PYROCONT1: U1.69 (PB10); also elsewhere on the board
PYROCONT2: U1.101 (PA9); also elsewhere on the board
PYROCONT3: U1.88 (PG3); also elsewhere on the board
PYRO_FIRE1: U1.70 (PB11); also elsewhere on the board
PYRO_FIRE2: U1.100 (PA8); also elsewhere on the board
PYRO_FIRE3: U1.89 (PG4); also elsewhere on the board
RF_BUSY: U1.45 (PC5); also elsewhere on the board
RF_CS: U1.40 (PA4); also elsewhere on the board
RF_MISO: U1.42 (PA6); also elsewhere on the board
RF_MOSI: U1.43 (PA7); also elsewhere on the board
RF_SCK: U1.41 (PA5); also elsewhere on the board
RPI_RX: U1.36 (PA2); also elsewhere on the board
RPI_TX: U1.37 (PA3); also elsewhere on the board
SCK_FLASH: U1.111 (PC10); also elsewhere on the board
SCK_IMU: U1.74 (PB13); also elsewhere on the board
SCL_BARO: U1.81 (PD12); also elsewhere on the board
SDA_BARO: U1.82 (PD13); also elsewhere on the board
VBAT7.4V: J6.1, J12.1, J12.2; also elsewhere on the board
VBUS: D3.1, J18.1 (VBUS)

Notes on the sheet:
SWD Programming
USB
VBUS from USB connector (nom. +5V) Min. 22uF i/o capacitors
LDO
MCU

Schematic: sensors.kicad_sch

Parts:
C36: 100n; C_0603_1608Metric
C39, C41, C42, C58: 100n; C_0402_1005Metric
C40: 2.2u; C_0402_1005Metric
C59: 10n; C_0402_1005Metric
J2: Conn_01x02_Pin; JST_XH_B2B-XH-A_1x02_P2.50mm_Vertical
J7: 532610471; MOLEX_532610471; PARTREV J; DigiKey_Part_Number WM7622CT-ND
R14, R17, R21, R22: 4.7k; R_0603_1608Metric
R32: 100Ω; R_0402_1005Metric
U3: BNO085; IC_BNO085; PARTREV v1.17
U4: ICM-42688-P; PQFN50P300X250X97-14N; PARTREV 1.2
U5: MS5611-01BA; LGA-8_3x5mm_P1.25mm

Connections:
+3V3: C36.1, C39.2, C40.2, C41.2, C42.2, C59.2, R14.1, R17.1, R21.1, R22.2, U3.3 (VDD), U3.28 (VDDIO), U4.5 (VDDIO), U4.8 (VDD), U5.1 (VDD), U5.2 (PS); also elsewhere on the board
+5V: J7.1; also elsewhere on the board
/Clocks/XINIMU: U3.27 (XIN32); also elsewhere on the board
/Clocks/XOUTIMU: U3.26 (XOUT32/CLKSEL1); also elsewhere on the board
BN_NRST: U3.11 (~RST); also elsewhere on the board
BN_SCL: R21.2, U3.19 (H_SCL/SCK/RX); also elsewhere on the board
BN_SDA: R22.1, U3.20 (H_SDA/H_MISO/TX); also elsewhere on the board
CAN_RX: J2.1; also elsewhere on the board
CAN_TX: J2.2; also elsewhere on the board
CS_IMU: U4.12 (AP_CS); also elsewhere on the board
GND: C36.2, C39.1, C40.1, C41.1, C42.1, C58.2, C59.1, J7.2, J7.S1 (SHIELD1), J7.S2 (SHIELD2), U3.2 (GND), U3.10 (CLKSEL0), U3.17 (SA0/H_MOSI), U3.25 (GNDIO), U4.6 (GND), U4.7 (RESV_7), U4.11 (RESV_11), U5.3 (GND), U5.4 (CSB), U5.5 (CSB); also elsewhere on the board
INT1_IMU: R32.2; also elsewhere on the board
LIDAR_RX: J7.4; also elsewhere on the board
LIDAR_TX: J7.3; also elsewhere on the board
MISO_IMU: U4.1 (AP_SDO/AP_AD0); also elsewhere on the board
MOSI_IMU: U4.14 (AP_SDA/AP_SDIO/AP_SDI); also elsewhere on the board
unnamed: C58.1, U3.9 (CAP)
unnamed: R32.1, U4.4 (INT1/INT)
SCK_IMU: U4.13 (AP_SCL/AP_SCLK); also elsewhere on the board
SCL_BARO: R17.2, U5.8 (SCLK); also elsewhere on the board
SDA_BARO: R14.2, U5.7 (SDI/SDA); also elsewhere on the board

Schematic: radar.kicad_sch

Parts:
C49, C66, C67: 100n; C_0402_1005Metric
C53: 10u; C_0402_1005Metric
IC7: A121-001-T&R; A121001TR; Mouser Part Number 925-A121-001-T&R
R15: 10k; R_0402_1005Metric
U7: TXS0108EPW; TSSOP-20_4.4x6.5mm_P0.65mm

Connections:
+1V8: C49.2, C53.2, C67.2, IC7.C2 (VRX_1), IC7.C9 (VTX_1), IC7.D1 (VRX_2), IC7.D10 (VTX_2), IC7.J1 (RESET_N), IC7.J9 (VDIG), IC7.K9 (VIO), U7.2 (VCCA); also elsewhere on the board
+3V3: C66.1, R15.1, U7.10 (OE), U7.19 (VCCB); also elsewhere on the board
/Clocks/XIN1: IC7.J10 (XIN); also elsewhere on the board
/Clocks/XOUT1: IC7.H10 (XOUT); also elsewhere on the board
/mmWave/1.8VCS: IC7.J2 (SPI_SS), U7.1 (A1)
/mmWave/1.8VMISO: IC7.K3 (SPI_MISO), U7.4 (A3)
/mmWave/1.8VMOSI: IC7.K6 (SPI_MOSI), U7.5 (A4)
/mmWave/1.8VSCK: IC7.K2 (SPI_CLK), U7.3 (A2)
Acc1: IC7.F10 (ENABLE), U7.6 (A5)
Enable_1: U7.15 (B5); also elsewhere on the board
GND: C49.1, C53.1, C66.2, C67.1, IC7.A3 (GND_1), IC7.A4 (GND_2), IC7.A5 (GND_3), IC7.A6 (GND_4), IC7.A7 (GND_5), IC7.A8 (GND_6), IC7.A9 (CTRL), IC7.B2 (GND_7), IC7.B9 (GND_8), IC7.B10 (GPIO3), IC7.C1 (GND_9), IC7.C10 (GND_10), IC7.D2 (GND_11), IC7.D9 (GND_12), IC7.E1 (GND_13), IC7.E2 (GND_14), IC7.E9 (GND_15), IC7.E10 (PLL_RF_TEST), IC7.F1 (GPIO1), IC7.F2 (GND_16), IC7.F9 (GND_17), IC7.G1 (GND_18), IC7.G10 (GND_19), IC7.H1 (GPIO2), IC7.H2 (GND_20), IC7.H9 (GND_21), IC7.J3 (GND_22), IC7.J5 (GND_23), IC7.J6 (GND_24), IC7.J8 (GND_25), IC7.K4 (GND_26), IC7.K5 (GPIO4), IC7.K7 (GND_27), U7.11 (GND); also elsewhere on the board
PCR_CS: R15.2, U7.17 (B3); also elsewhere on the board
PCR_MISO: U7.18 (B2); also elsewhere on the board
PCR_MOSI: U7.20 (B1); also elsewhere on the board
PCR_SCK: U7.16 (B4); also elsewhere on the board
